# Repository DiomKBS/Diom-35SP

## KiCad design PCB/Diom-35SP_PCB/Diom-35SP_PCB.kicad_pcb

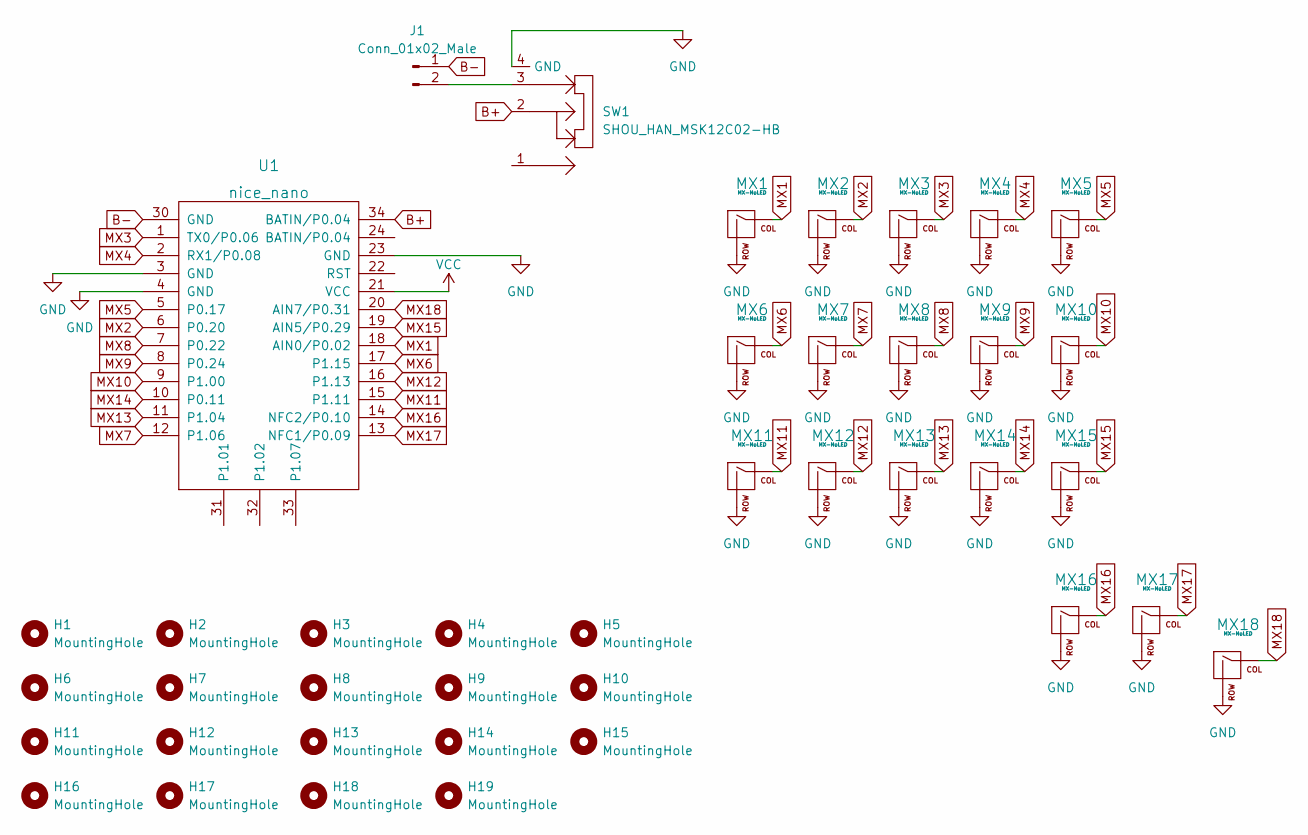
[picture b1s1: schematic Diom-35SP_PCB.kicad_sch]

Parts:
H1, H2, H3, H4, H5, H6, H7, H8, H9, H10, H11, H12, H13, H14, H15, H16, H17, H18, H19: MountingHole; MountingHole_2.2mm_M2_DIN965
J1: Conn_01x02_Male; JST_EH_S2B-EH_1x02_P2.50mm_Horizontal
MX1, MX2, MX3, MX4, MX5, MX6, MX7, MX8, MX9, MX10, MX11, MX12, MX13, MX14, MX15, MX16: MX-NoLED; CherryMX-1U-doubleSided-noSilk
MX17, MX18: MX-NoLED; CherryMX-1.5U-doubleSided-Vertical-noSilk
SW1: SHOU_HAN_MSK12C02-HB; SHOU HAN MSK12C02-HB
U1: nice_nano

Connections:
B+: SW1.2, U1.34 (BATIN/P0.04)
B-: J1.1, U1.30 (GND)
GND: MX1.2 (ROW), MX2.2 (ROW), MX3.2 (ROW), MX4.2 (ROW), MX5.2 (ROW), MX6.2 (ROW), MX7.2 (ROW), MX8.2 (ROW), MX9.2 (ROW), MX10.2 (ROW), MX11.2 (ROW), MX12.2 (ROW), MX13.2 (ROW), MX14.2 (ROW), MX15.2 (ROW), MX16.2 (ROW), MX17.2 (ROW), MX18.2 (ROW), SW1.4 (GND), U1.3 (GND), U1.4 (GND), U1.23 (GND)
MX1: MX1.1 (COL), U1.18 (AIN0/P0.02)
MX2: MX2.1 (COL), U1.6 (P0.20)
MX3: MX3.1 (COL), U1.1 (TX0/P0.06)
MX4: MX4.1 (COL), U1.2 (RX1/P0.08)
MX5: MX5.1 (COL), U1.5 (P0.17)
MX6: MX6.1 (COL), U1.17 (P1.15)
MX7: MX7.1 (COL), U1.12 (P1.06)
MX8: MX8.1 (COL), U1.7 (P0.22)
MX9: MX9.1 (COL), U1.8 (P0.24)
MX10: MX10.1 (COL), U1.9 (P1.00)
MX11: MX11.1 (COL), U1.15 (P1.11)
MX12: MX12.1 (COL), U1.16 (P1.13)
MX13: MX13.1 (COL), U1.11 (P1.04)
MX14: MX14.1 (COL), U1.10 (P0.11)
MX15: MX15.1 (COL), U1.19 (AIN5/P0.29)
MX16: MX16.1 (COL), U1.14 (NFC2/P0.10)
MX17: MX17.1 (COL), U1.13 (NFC1/P0.09)
MX18: MX18.1 (COL), U1.20 (AIN7/P0.31)
unnamed: J1.2, SW1.3
VCC: U1.21 (VCC)

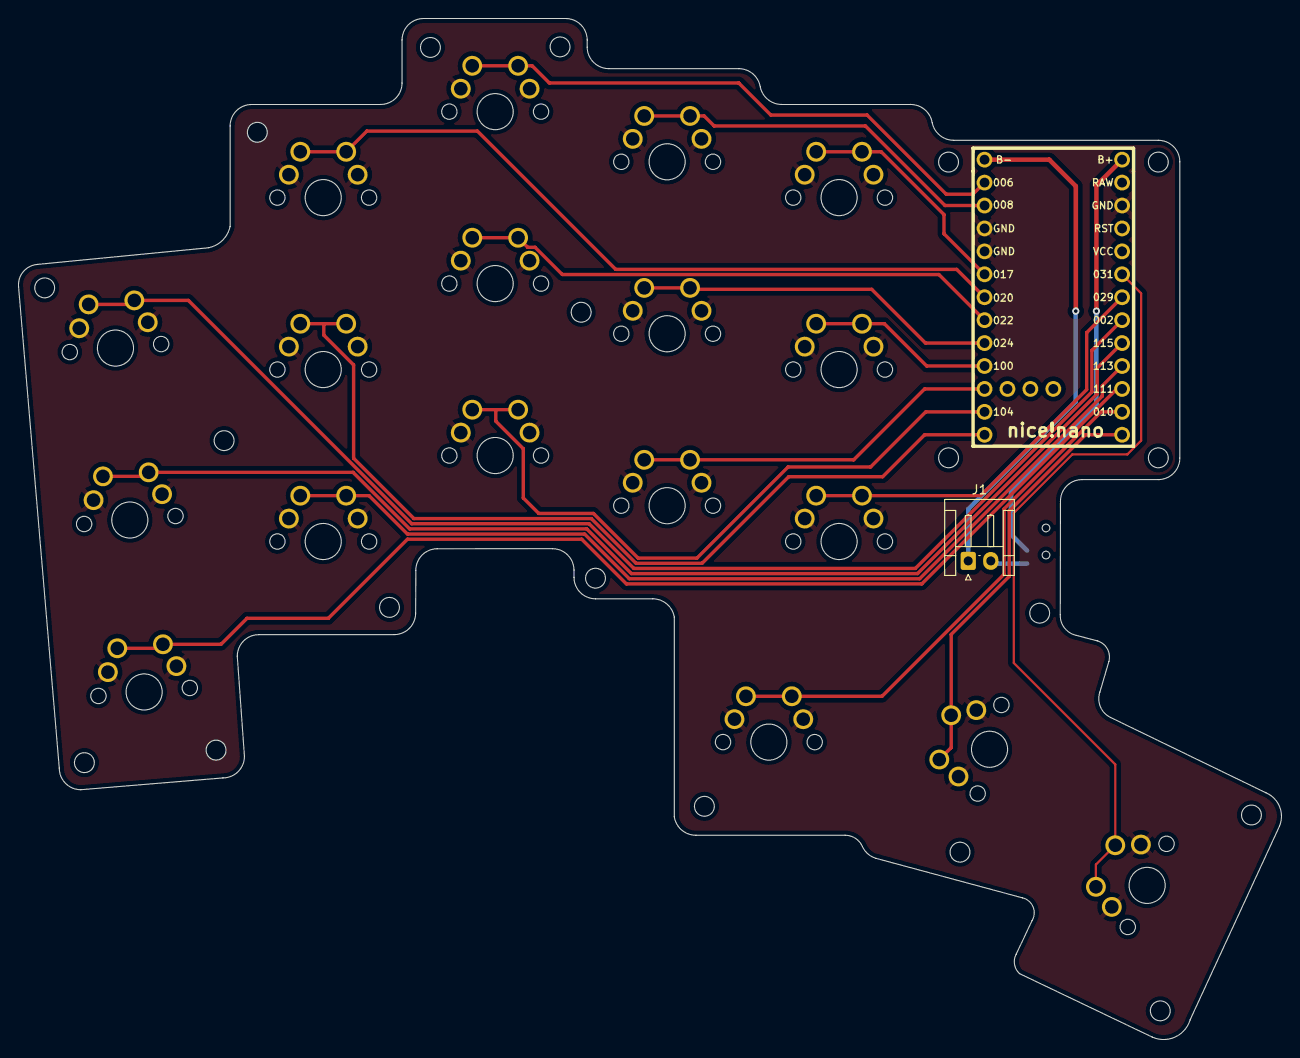
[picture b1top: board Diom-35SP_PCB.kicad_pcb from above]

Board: 2 copper layers, 139.9 x 113.1 mm, 40 parts (1 on the bottom side), 22 nets.

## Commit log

2022-05-02 Finished basic Layout
    +All Keys wired
    -Battery power not yet wired
2022-05-03 Wired Battery Connector, 1.5U Thumb Key
2022-05-04 Mounting Holes added
2022-05-04 Copper Mask Art added
2022-05-04 Added On/Off Switch
2022-05-05 Moved Artwork, Tracks, Rounded PCB
    Also Gerbers
2022-05-05 Added Teardrops to Rounded PCB
2022-05-05 New Gerber for Rounded PCB
2022-05-15 super kuhl images
2022-05-15 Massive Changes
    -New Switch
    -New Outline
    -More Mounting Holes
2022-05-15 Finished Renaming to 35SP
2022-05-16 berserk images
2022-05-16 some textures
2022-05-24 some cleanups
2022-05-24 3d Models and Blender File
2022-05-26 still not finished
2022-05-26 3d Models, New Footprints for Switches
2022-05-27 Changed 3d Models
2022-05-28 rendered out
2022-06-27 final gerber generation
